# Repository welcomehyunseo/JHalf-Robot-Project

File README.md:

# JHalf-Robot-Project
We will make 2 legs robot with raspberry pi

To do that we needs below.

1. raspberry pi 4 8gb (Maybe it is over power)
2. servo motor (wittstand a high weight.)
3. link frame (which made 3d printer)

## How to control this??
Raspberry pi will open the server this named react and flask.

Flask is python server and we need python code.
React is control UI.

## What's the react UI control function?

## What's the flask server jop?

asdfasdf

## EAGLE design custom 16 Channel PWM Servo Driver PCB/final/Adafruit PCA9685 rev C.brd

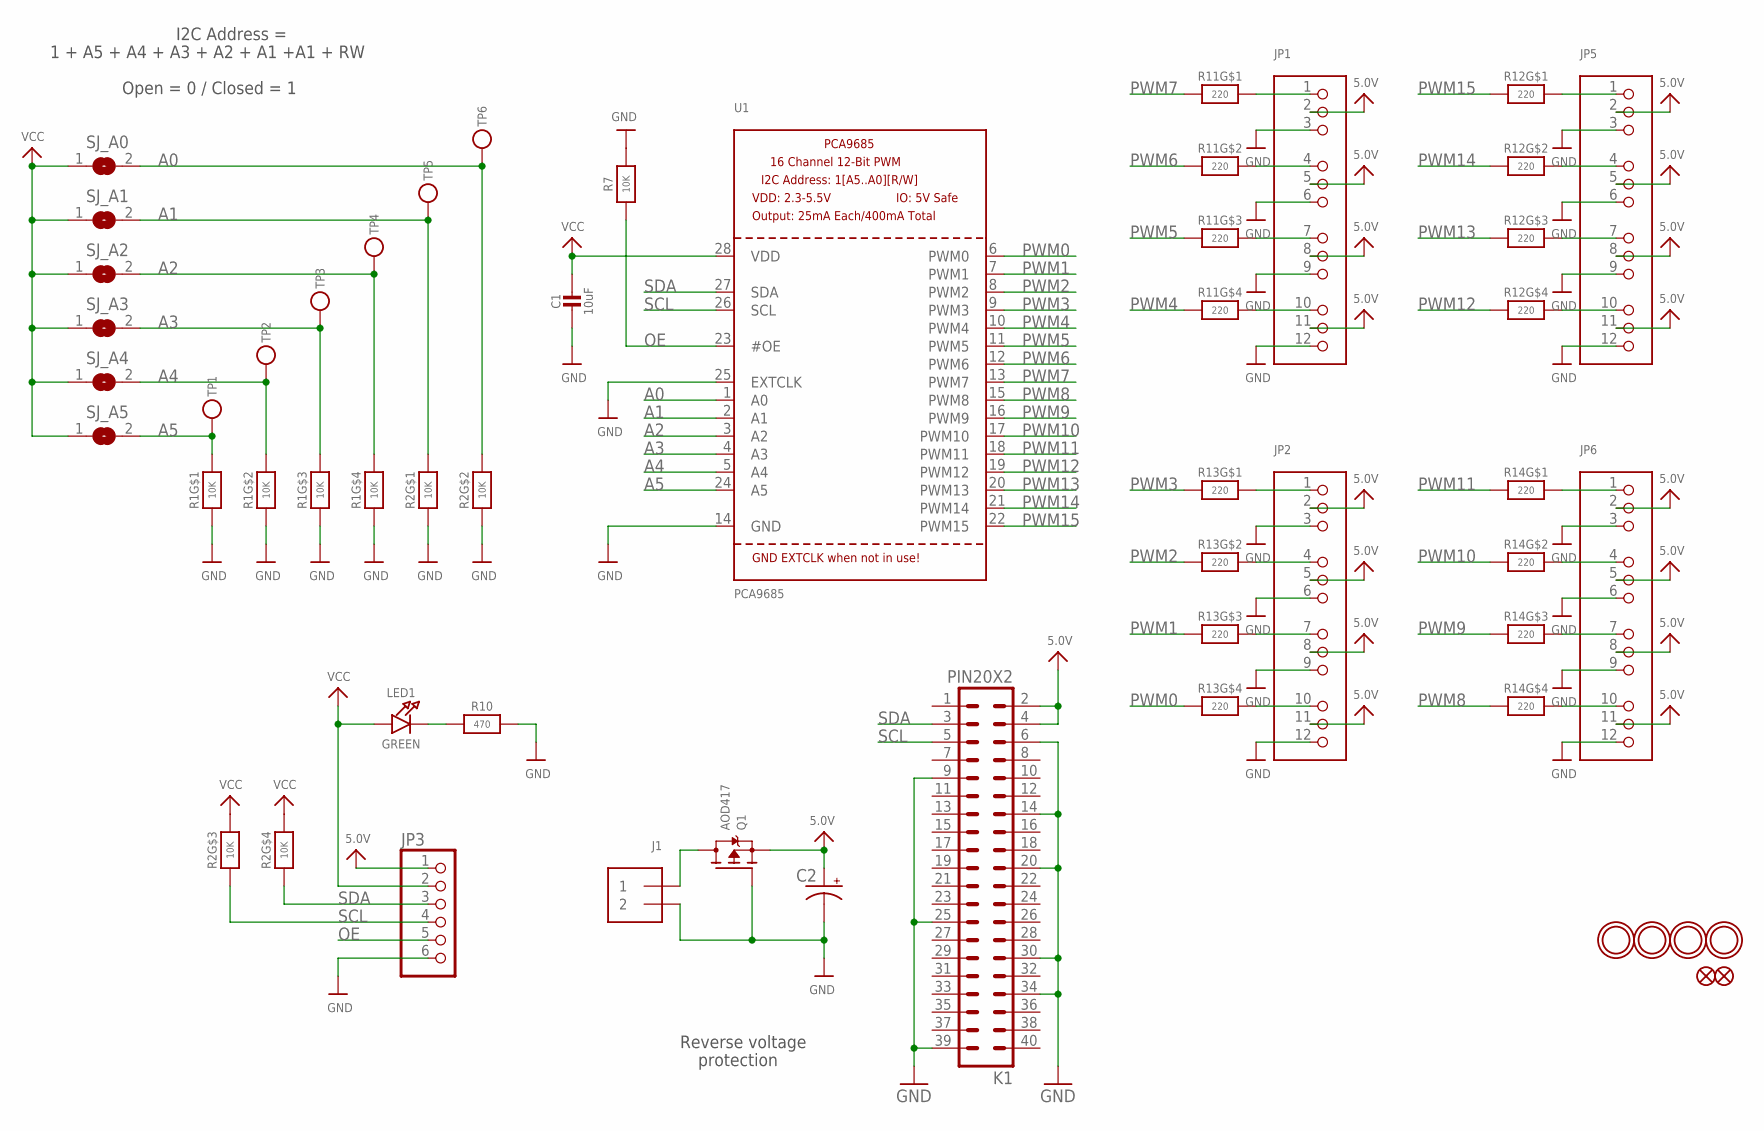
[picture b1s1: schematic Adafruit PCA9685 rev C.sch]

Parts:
C1: 10uF; 0805-NO
C2: CPOL-USE3.5-8; E3,5-8
FID1, FID2: FIDUCIAL""; FIDUCIAL_1MM
J1: TERMBLOCK_1X2; TERMBLOCK_1X2-3.5MM
JP1, JP2, JP5, JP6: HEADER-3X04; 3X04
JP3: PINHD-1X6CB; 1X06-CLEANBIG
K1: PIN20X2; PIN_20X2
LED1: GREEN; CHIPLED_0805_NOOUTLINE
Q1: AOD417; TO252
R1, R2: 10K; RESPACK_4X0603
R7: 10K; 0805-NO
R10: 470; _0805MP
R11, R12, R13, R14: 220; RESPACK_4X0603
SJ_A0, SJ_A1, SJ_A2, SJ_A3, SJ_A4, SJ_A5: SOLDERJUMPERREFLOW_NOPASTE; SOLDERJUMPER_REFLOW_NOPASTE
TP1, TP2, TP3, TP4, TP5, TP6: TESTPOINTROUND1MM; TESTPOINT_ROUND_1MM
U1: PCA9685; TSSOP28
U$47, U$48, U$49, U$50: MOUNTINGHOLE2.5; MOUNTINGHOLE_2.5_PLATED

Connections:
5.0V: C2.+, JP1.2, JP1.5, JP1.8, JP1.11, JP2.2, JP2.5, JP2.8, JP2.11, JP3.1, JP5.2, JP5.5, JP5.8, JP5.11, JP6.2, JP6.5, JP6.8, JP6.11, K1.2, K1.4, Q1.2 (S)
A0: R2.7 (2), SJ_A0.2, TP6.P$1, U1.1 (A0)
A1: R2.8 (2), SJ_A1.2, TP5.P$1, U1.2 (A1)
A2: R1.5 (2), SJ_A2.2, TP4.P$1, U1.3 (A2)
A3: R1.6 (2), SJ_A3.2, TP3.P$1, U1.4 (A3)
A4: R1.7 (2), SJ_A4.2, TP2.P$1, U1.5 (A4)
A5: R1.8 (2), SJ_A5.2, TP1.P$1, U1.24 (A5)
GND: C1.2, C2.-, J1.2, JP1.3, JP1.6, JP1.9, JP1.12, JP2.3, JP2.6, JP2.9, JP2.12, JP3.6, JP5.3, JP5.6, JP5.9, JP5.12, JP6.3, JP6.6, JP6.9, JP6.12, K1.6, K1.9, K1.14, K1.20, K1.25, K1.30, K1.34, K1.39, Q1.1 (G), R1.1, R1.2 (1), R1.3 (1), R1.4 (1), R2.1, R2.2 (1), R7.2, R10.2, U1.14 (GND), U1.25 (EXTCLK)
unnamed: LED1.C, R10.1
unnamed: JP1.4, R11.7 (2)
unnamed: JP1.1, R11.8 (2)
unnamed: JP1.7, R11.6 (2)
unnamed: JP1.10, R11.5 (2)
unnamed: JP2.1, R13.8 (2)
unnamed: JP2.4, R13.7 (2)
unnamed: JP2.7, R13.6 (2)
unnamed: JP2.10, R13.5 (2)
unnamed: JP6.10, R14.5 (2)
unnamed: JP6.7, R14.6 (2)
unnamed: JP6.4, R14.7 (2)
unnamed: JP6.1, R14.8 (2)
unnamed: JP5.10, R12.5 (2)
unnamed: JP5.7, R12.6 (2)
unnamed: JP5.4, R12.7 (2)
unnamed: JP5.1, R12.8 (2)
OE: JP3.5, R7.1, U1.23 (#OE)
PWM0: R13.4 (1), U1.6 (PWM0)
PWM1: R13.3 (1), U1.7 (PWM1)
PWM2: R13.2 (1), U1.8 (PWM2)
PWM3: R13.1, U1.9 (PWM3)
PWM4: R11.4 (1), U1.10 (PWM4)
PWM5: R11.3 (1), U1.11 (PWM5)
PWM6: R11.2 (1), U1.12 (PWM6)
PWM7: R11.1, U1.13 (PWM7)
PWM8: R14.4 (1), U1.15 (PWM8)
PWM9: R14.3 (1), U1.16 (PWM9)
PWM10: R14.2 (1), U1.17 (PWM10)
PWM11: R14.1, U1.18 (PWM11)
PWM12: R12.4 (1), U1.19 (PWM12)
PWM13: R12.3 (1), U1.20 (PWM13)
PWM14: R12.2 (1), U1.21 (PWM14)
PWM15: R12.1, U1.22 (PWM15)
PWRIN: J1.1, Q1.3 (D)
SCL: JP3.4, K1.5, R2.3 (1), U1.26 (SCL)
SDA: JP3.3, K1.3, R2.4 (1), U1.27 (SDA)
VCC: C1.1, JP3.2, LED1.A, R2.5 (2), R2.6 (2), SJ_A0.1, SJ_A1.1, SJ_A2.1, SJ_A3.1, SJ_A4.1, SJ_A5.1, U1.28 (VDD)

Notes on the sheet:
Reverse voltage
protection
1 + A5 + A4 + A3 + A2 + A1 +A1 + RW
I2C Address =
Open = 0 / Closed = 1

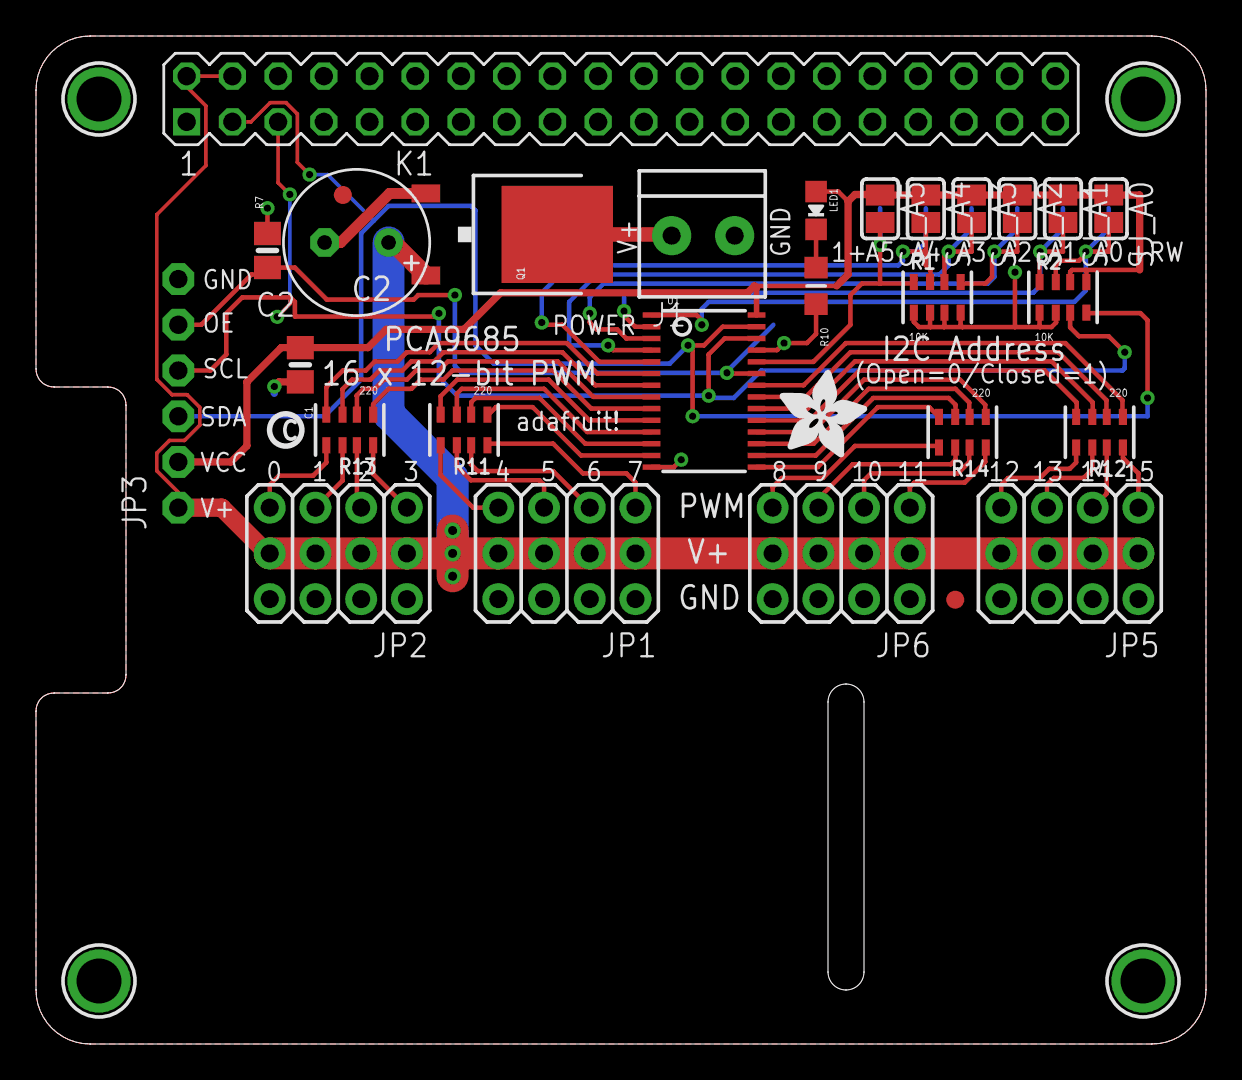
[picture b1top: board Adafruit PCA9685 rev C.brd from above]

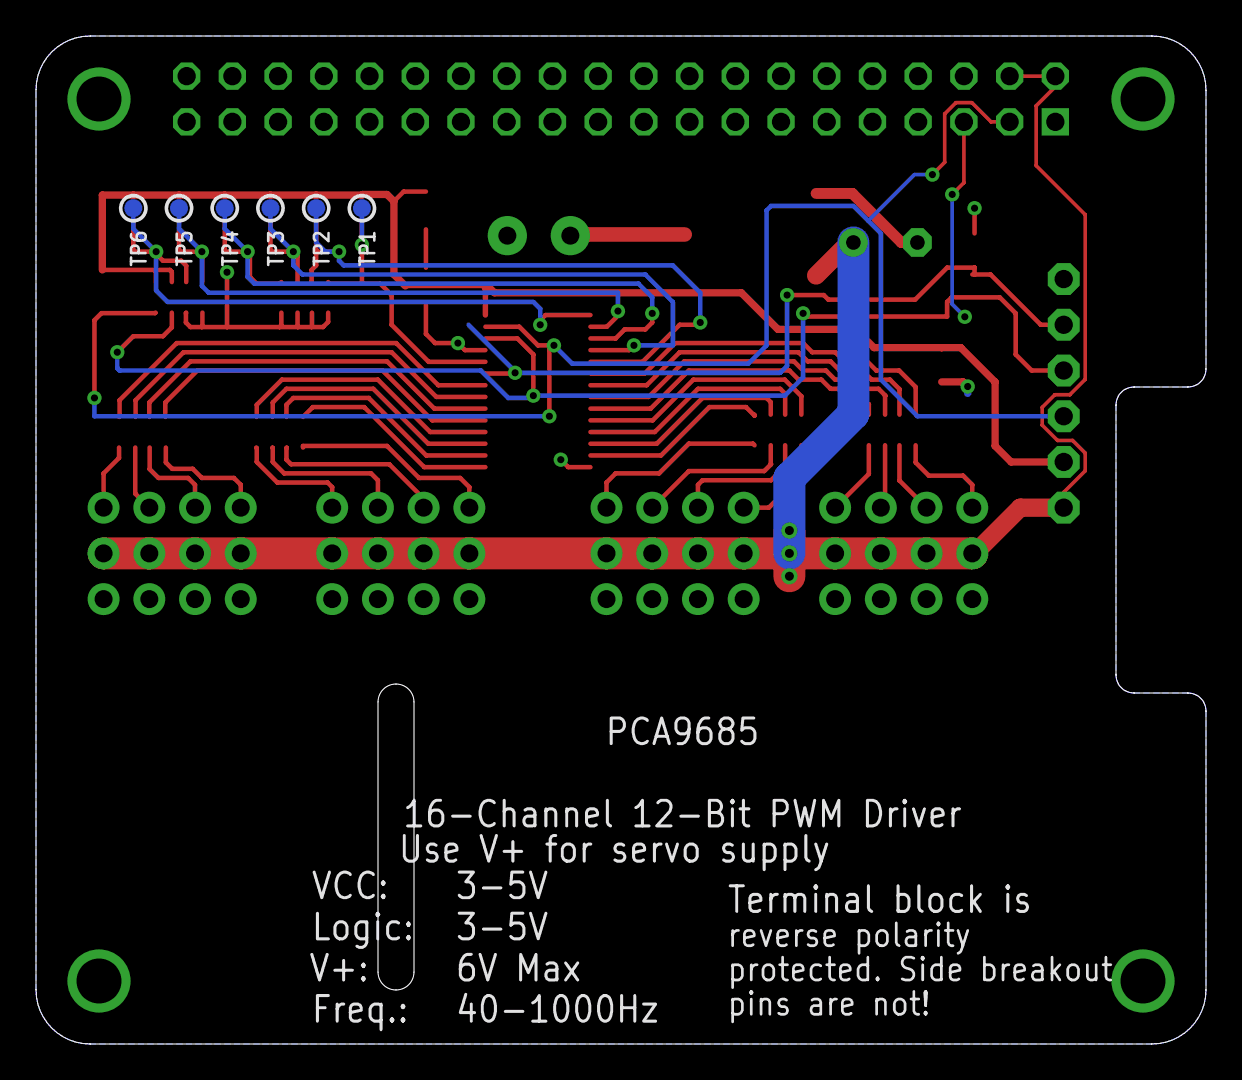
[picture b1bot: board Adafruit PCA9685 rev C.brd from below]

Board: 2 copper layers, 65.0 x 56.0 mm, 40 parts (6 on the bottom side), 46 nets.

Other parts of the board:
U$51: ADAFRUIT_5MM
U$54: PCBFEAT-REV-040

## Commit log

2020-11-13 부품목록 정리
2020-11-13 필요개수 항목 추가
2020-11-13 서보 다중 제어 회로 기판 문서 추가
2020-11-13 부품추가
    서보모터 다중제어 모듈
2020-11-13 부품 수정
2020-11-16 파트 업데이트
2020-11-22 부품 업데이트
2020-11-22 3d 모델링 업로드
2020-11-28 mg996r modeling
2020-11-28 adding barring position
